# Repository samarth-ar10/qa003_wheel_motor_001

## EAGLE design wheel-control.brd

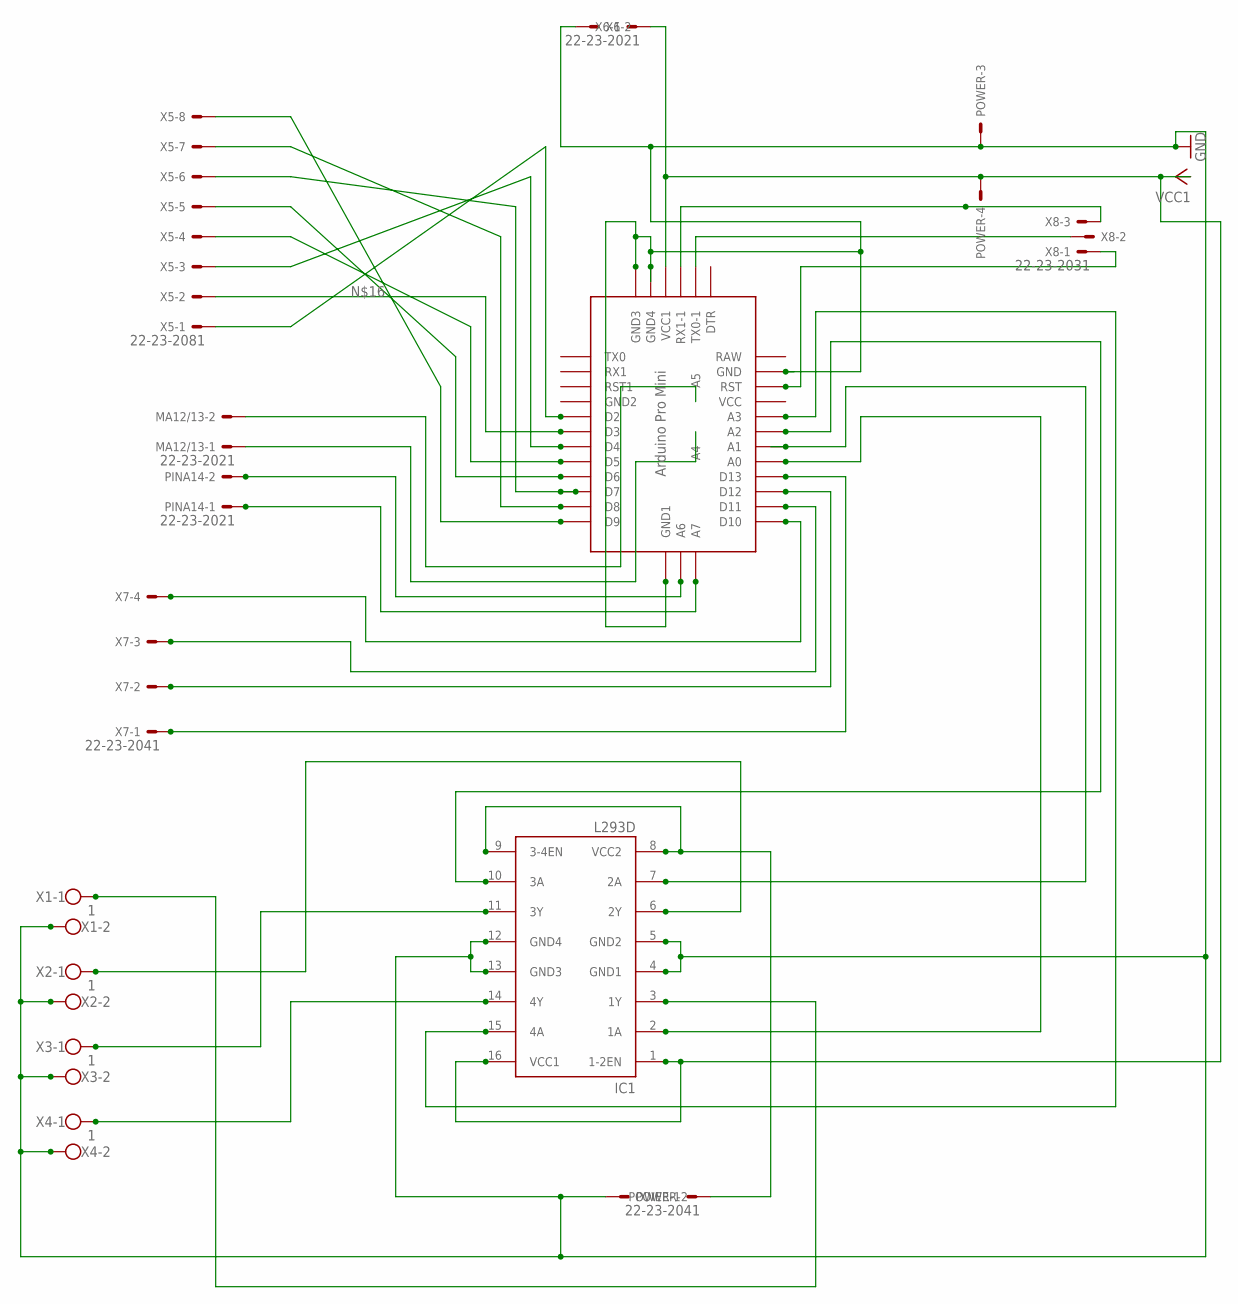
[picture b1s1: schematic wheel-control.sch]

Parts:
IC1: L293D; DIL16
MA12/13: 22-23-2021
PINA14: 22-23-2021
POWER: 22-23-2041
U$1: ABK-PRO-MINI
X1, X2, X3, X4: 1; W237-102
X5: 22-23-2081
X6: 22-23-2021
X7: 22-23-2041
X8: 22-23-2031

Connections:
GND: IC1.4 (GND1), IC1.5 (GND2), IC1.12 (GND4), IC1.13 (GND3), POWER.2, POWER.3, U$1.GND, U$1.GND2 (GND3), U$1.GND3 (GND4), U$1.GND4 (GND1), X1.2, X2.2, X3.2, X4.2, X6.2
unnamed: U$1.TX0-1, X8.2
unnamed: IC1.15 (4A), U$1.A3
unnamed: U$1.D10, X7.4
unnamed: IC1.10 (3A), U$1.A2
unnamed: U$1.RST, X8.1
unnamed: IC1.11 (3Y), X3.1
unnamed: U$1.D4, X5.3
unnamed: U$1.D7, X5.6
unnamed: U$1.D8, X5.7
unnamed: U$1.D2, X5.1
unnamed: U$1.D3, X5.2
unnamed: U$1.D5, X5.4
unnamed: U$1.D6, X5.5
unnamed: U$1.D9, X5.8
unnamed: MA12/13.2, U$1.A5
unnamed: MA12/13.1, U$1.A4
unnamed: PINA14.2, U$1.A6
unnamed: PINA14.1, U$1.A7
unnamed: IC1.7 (2A), U$1.A1
unnamed: U$1.RX1-1, X8.3
unnamed: U$1.D11, X7.3
unnamed: U$1.D12, X7.2
unnamed: U$1.D13, X7.1
unnamed: IC1.8 (VCC2), IC1.9 (3-4EN), POWER.1
unnamed: IC1.14 (4Y), X4.1
unnamed: IC1.3 (1Y), X1.1
unnamed: IC1.6 (2Y), X2.1
unnamed: IC1.2 (1A), U$1.A0
VCC: IC1.1 (1-2EN), IC1.16 (VCC1), POWER.4, U$1.VCC1, X6.1

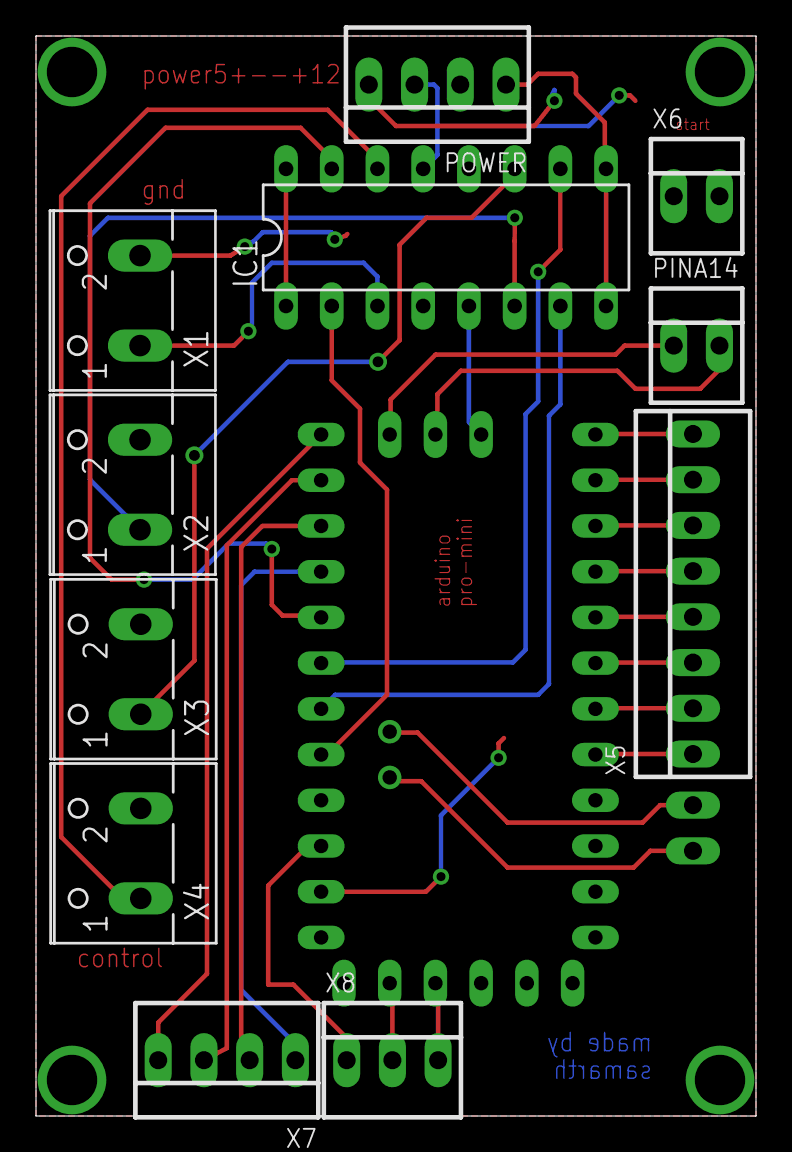
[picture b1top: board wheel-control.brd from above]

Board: 2 copper layers, 40.0 x 60.0 mm, 13 parts (1 on the bottom side), 30 nets.

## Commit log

2020-03-01 pushing files to GitHub
2020-03-15 Adding Images
2020-11-09 Adding stl file
